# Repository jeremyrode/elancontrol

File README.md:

# elancontrol
### Code to control an Elan System6 Integrated Multi-Zone Controller from RaspberryPi

## FYI, I'm currently [porting the ZPad command generation to a Raspberry Pi Pico](https://github.com/jeremyrode/pico_elancontrol)

## What's in this repository:
- commandlinetools: low level software to test the bit-banging Software
- docs: notes / pictures / MATLAB data
- InterfacePCB: Eagle Files to build RaspberryPi HAT interface to the 6 x RJ-45 connectors
- nodejsserver: Code for the control system

### Hardware:

- [x] Reverse Engineer IR Control Protocol
- [x] Create Function to Replicate IR Control on RaspPi GPIO
- [x] Design Electrical Level Shifter for IR Protocol
- [x] Write UDP server that listens for commands and sends via GPIO
- [x] Verify GPIOs can be used on Pi2
- [x] Verify RS-485 identical on all 6 zones.
- [x] Design RaspPi "Hat" PCB with 6 x Level Shifters and 1 x RS-485
- [x] Test RaspPi "Hat"

### Software:

- [x] Interface Node.js to bit banging C software via N-API
- [x] Node.js server via Websockets
- [x] Webpage GUI with Websockets interface to the Node.js backend
- [x] Reverse Engineer RS-485 based Status Protocol to display current state

## Current Status
Full command sending functionality achieved:

HTML Frontend /JavaScript ->  Websocket -> Node.js Sever -> Via N-API -> C Bitbang GPIO -> Custom Level Shifter pcb

Status packet and reporting functionality achieved:

 RS-485 -> SerialPort (node.js) -> Delimiter Parser (node.js) -> Websocket -> HTML Frontend /JavaScript

## General Info
I have a Elan S6 in my house and I love it, if only I could control it via my phone!  It shouldn't be that hard to get a Pi connected!

## Inital Feasibility
This initial goal is to have a Raspberry inject IR commands from a bit banged GPIO.  I'm going to capture the commands from the Zpad, and see if a Pi can bit bang fast enough to replicate them.  Unfortunately, it looks like pin#2 uses an open collector pull up to 12V.  We will need a level shifter and a PMOS pull-up.  I will build a level shifter, and test if we can command the S6

Looking at the commands, they consist of 12 x 12.5 us wide 12V high pulses, with either 5.07 ms spacing (short) or 7.6 ms of spacing (long).
The first 6 pulses seem to be a preamble, always spaced short, then the next 6 with either long or short:

Decoding of the Key Commands (Preamble Omitted):

| Command  | Code | Bin | Dec |
| :------: |:----:|:---:|:---:|
| Power | SSSSSS | 000000 | 0 |
| Mute | SSSSLS | 000010 | 2 |
| VolUp | SSSLSS | 000100 | 4 |
| VolDown | LSSLSS | 100100 | 36 |
| 2ndRowRight | LSLSSS | 101000 | 40 |
| 2ndRowCenter | SSLLSS | 001100 | 12 |
| 2ndRowLeft | SSLSLL | 001011 | 11 |
| UpperRight | SSLSLS | 001010 | 10 |
| UpperCenter | SSLSSL | 001001 | 9 |
| UpperLeft | SSLSSS | 001000 | 8 |

## Level Shifter

Circuit takes the 3.3V GPIO from the Pi, and preforms a open-collector pull-up.  The S6 seems to have an internal 1k pull-down to ground.  Looking at the Zpads, they have an open-collector pull-up with a ~100 ohm resistor to current limit.  Added a dual diode for over-voltage protection (The Zpads have diode protection as well).

I also prototyped it with some components I had laying around:

## PCB

Trusty old Macrofab!

Known issues:  The bottom row of Cat5 Is hard to get out, as the Cat5 connectors are supposed to hang off the edge of the PCB.  This would make the PCB huge, if I'm still trying to use all 4 mounting holes.  No good way to solve this.  Need a very high [Rasperry Pi connector](https://www.amazon.com/gp/product/B0756KM3GB/ref=oh_aui_search_detailpage?ie=UTF8&psc=1) to clear (this one is barley tall enough).

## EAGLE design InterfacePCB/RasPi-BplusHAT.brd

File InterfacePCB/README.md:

# PCB
For some reason this is an incompleate version?

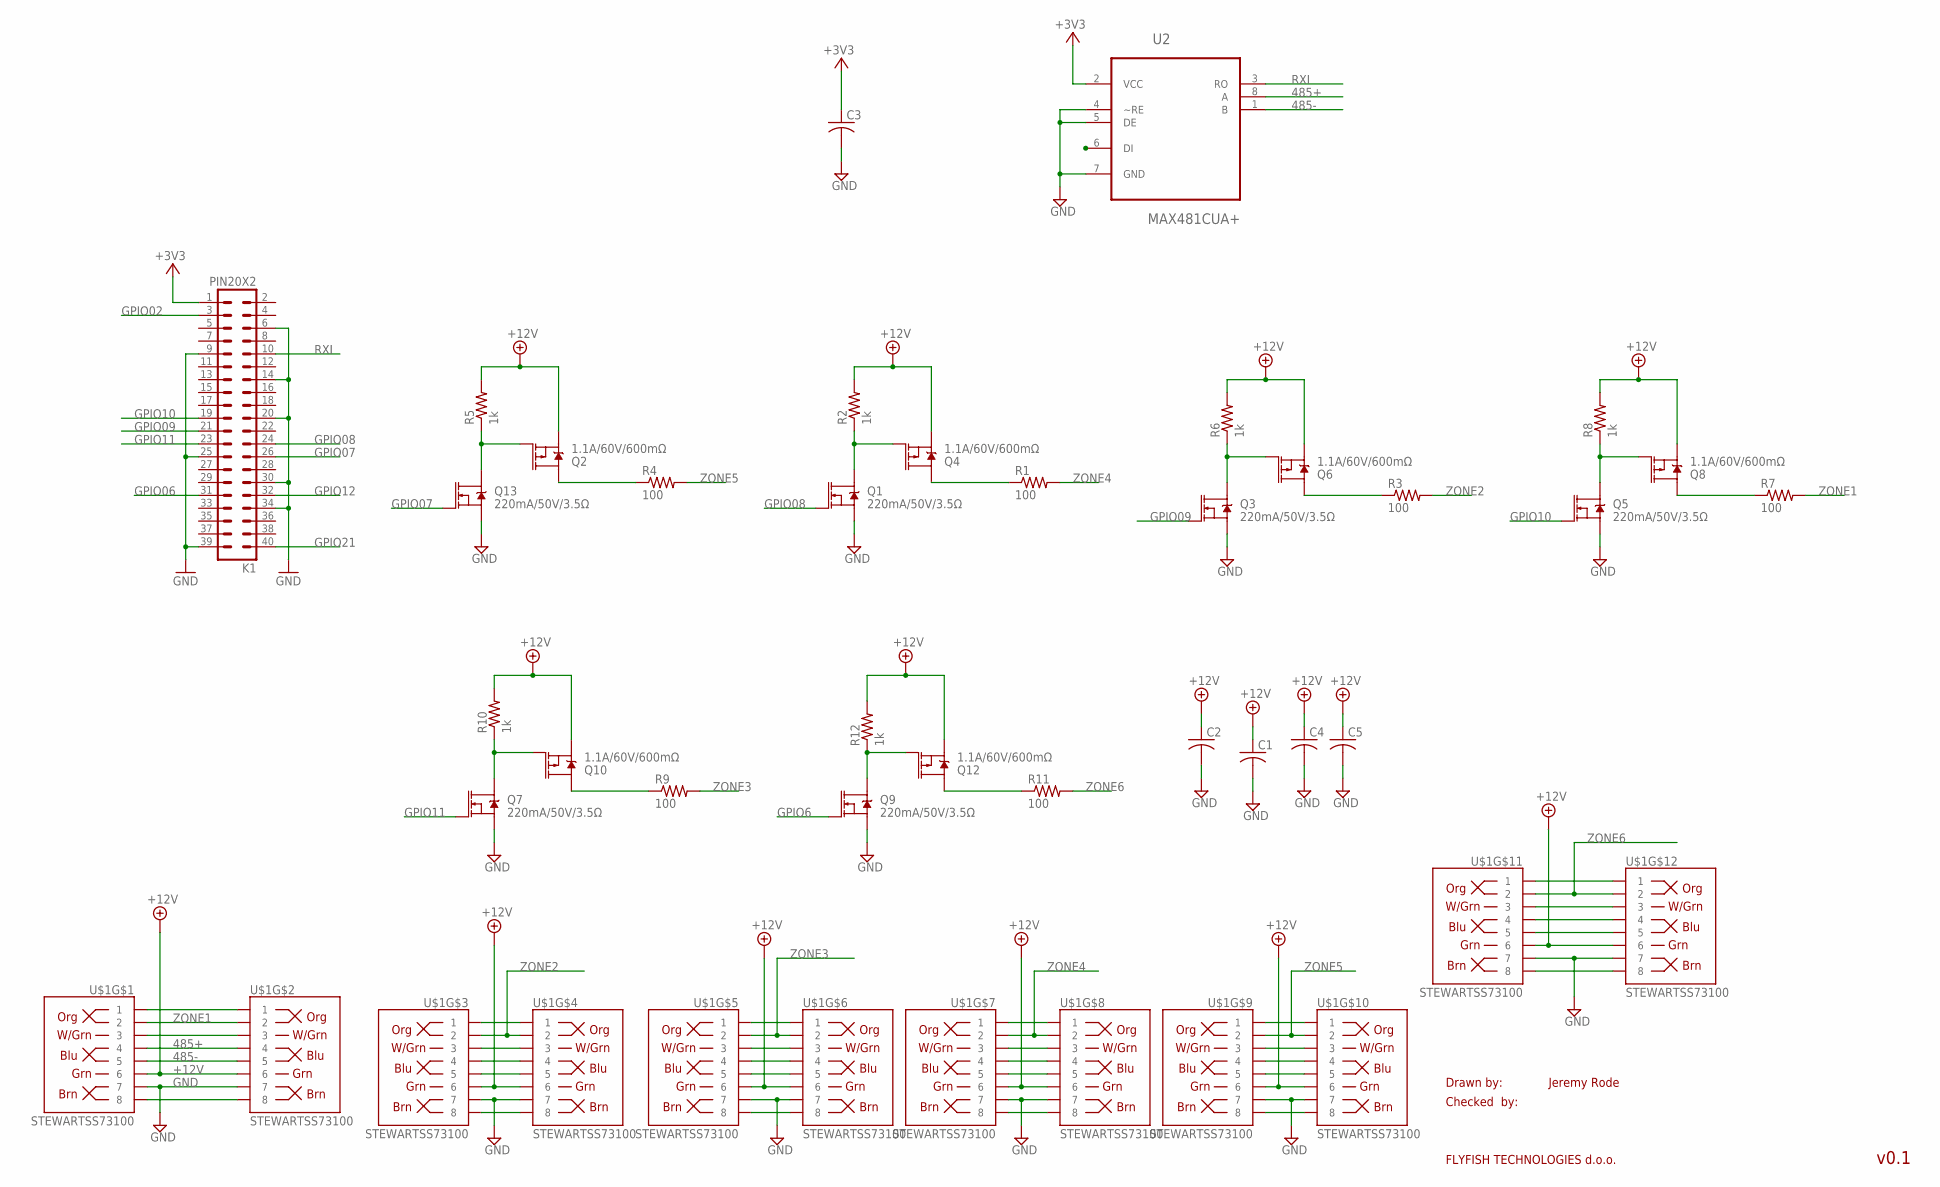
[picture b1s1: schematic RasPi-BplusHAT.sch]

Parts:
C1, C2, C3, C4, C5: C-USC0805; C0805
K1: PIN20X2; PIN_20X2
Q1, Q3, Q5, Q7, Q9, Q13: 220mA/50V/3.5Ω; SOT23-3
Q2, Q4, Q6, Q8, Q10, Q12: 1.1A/60V/600mΩ; SOT23-3
R1, R3, R4, R7, R9, R11: 100; R0805
R2, R5, R6, R8, R10, R12: 1k; R0805
U2: MAX481CUA+; SOP65P490X110-8N
U$1: STEWARTSS73100

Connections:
485+: U2.8 (A), U$1.P$4 (4), U$1.P$12 (4)
485-: U2.1 (B), U$1.P$5 (5), U$1.P$13 (5)
+3V3: C3.1, K1.1, U2.2 (VCC)
+12V: C1.1, C2.1, C4.1, C5.1, Q2.2 (S), Q4.2 (S), Q6.2 (S), Q8.2 (S), Q10.2 (S), Q12.2 (S), R2.2, R5.2, R6.2, R8.2, R10.2, R12.2, U$1.P$6 (6), U$1.P$14 (6), U$1.P$22 (6), U$1.P$30 (6), U$1.P$38 (6), U$1.P$46 (6), U$1.P$54 (6), U$1.P$62 (6), U$1.P$70 (6), U$1.P$78 (6), U$1.P$86 (6), U$1.P$94 (6)
GND: C1.2, C2.2, C3.2, C4.2, C5.2, K1.6, K1.9, K1.14, K1.20, K1.25, K1.30, K1.34, K1.39, Q1.2 (S), Q3.2 (S), Q5.2 (S), Q7.2 (S), Q9.2 (S), Q13.2 (S), U2.4 (~RE), U2.5 (DE), U2.7 (GND), U$1.P$7 (7), U$1.P$15 (7), U$1.P$23 (7), U$1.P$31 (7), U$1.P$39 (7), U$1.P$47 (7), U$1.P$55 (7), U$1.P$63 (7), U$1.P$71 (7), U$1.P$79 (7), U$1.P$87 (7), U$1.P$95 (7)
GPIO02: K1.3
GPIO6: Q9.1 (G)
GPIO06: K1.31
GPIO07: K1.26, Q13.1 (G)
GPIO08: K1.24, Q1.1 (G)
GPIO09: K1.21, Q3.1 (G)
GPIO10: K1.19, Q5.1 (G)
GPIO11: K1.23, Q7.1 (G)
GPIO12: K1.32
GPIO21: K1.40
unnamed: Q1.3 (D), Q4.1 (G), R2.1
unnamed: Q4.3 (D), R1.1
unnamed: Q3.3 (D), Q6.1 (G), R6.1
unnamed: Q2.1 (G), Q13.3 (D), R5.1
unnamed: Q2.3 (D), R4.1
unnamed: Q6.3 (D), R3.1
unnamed: Q5.3 (D), Q8.1 (G), R8.1
unnamed: Q8.3 (D), R7.1
unnamed: Q7.3 (D), Q10.1 (G), R10.1
unnamed: Q10.3 (D), R9.1
unnamed: Q9.3 (D), Q12.1 (G), R12.1
unnamed: Q12.3 (D), R11.1
unnamed: U$1.P$1 (1), U$1.P$9 (1)
unnamed: U$1.P$3 (3), U$1.P$11 (3)
unnamed: U$1.P$17 (1), U$1.P$25 (1)
unnamed: U$1.P$19 (3), U$1.P$27 (3)
unnamed: U$1.P$20 (4), U$1.P$28 (4)
unnamed: U$1.P$21 (5), U$1.P$29 (5)
unnamed: U$1.P$33 (1), U$1.P$41 (1)
unnamed: U$1.P$35 (3), U$1.P$43 (3)
unnamed: U$1.P$36 (4), U$1.P$44 (4)
unnamed: U$1.P$37 (5), U$1.P$45 (5)
unnamed: U$1.P$8 (8), U$1.P$16 (8)
unnamed: U$1.P$49 (1), U$1.P$57 (1)
unnamed: U$1.P$51 (3), U$1.P$59 (3)
unnamed: U$1.P$52 (4), U$1.P$60 (4)
unnamed: U$1.P$53 (5), U$1.P$61 (5)
unnamed: U$1.P$65 (1), U$1.P$73 (1)
unnamed: U$1.P$67 (3), U$1.P$75 (3)
unnamed: U$1.P$68 (4), U$1.P$76 (4)
unnamed: U$1.P$69 (5), U$1.P$77 (5)
unnamed: U$1.P$81 (1), U$1.P$89 (1)
unnamed: U$1.P$83 (3), U$1.P$91 (3)
unnamed: U$1.P$84 (4), U$1.P$92 (4)
unnamed: U$1.P$85 (5), U$1.P$93 (5)
unnamed: U$1.P$24 (8), U$1.P$32 (8)
unnamed: U$1.P$40 (8), U$1.P$48 (8)
unnamed: U$1.P$56 (8), U$1.P$64 (8)
unnamed: U$1.P$72 (8), U$1.P$80 (8)
unnamed: U$1.P$88 (8), U$1.P$96 (8)
RXI: K1.10, U2.3 (RO)
ZONE1: R7.2, U$1.P$2 (2), U$1.P$10 (2)
ZONE2: R3.2, U$1.P$18 (2), U$1.P$26 (2)
ZONE3: R9.2, U$1.P$34 (2), U$1.P$42 (2)
ZONE4: R1.2, U$1.P$50 (2), U$1.P$58 (2)
ZONE5: R4.2, U$1.P$66 (2), U$1.P$74 (2)
ZONE6: R11.2, U$1.P$82 (2), U$1.P$90 (2)

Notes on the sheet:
Drawn by:
Checked by:
FLYFISH TECHNOLOGIES d.o.o.
Jeremy Rode
v0.1

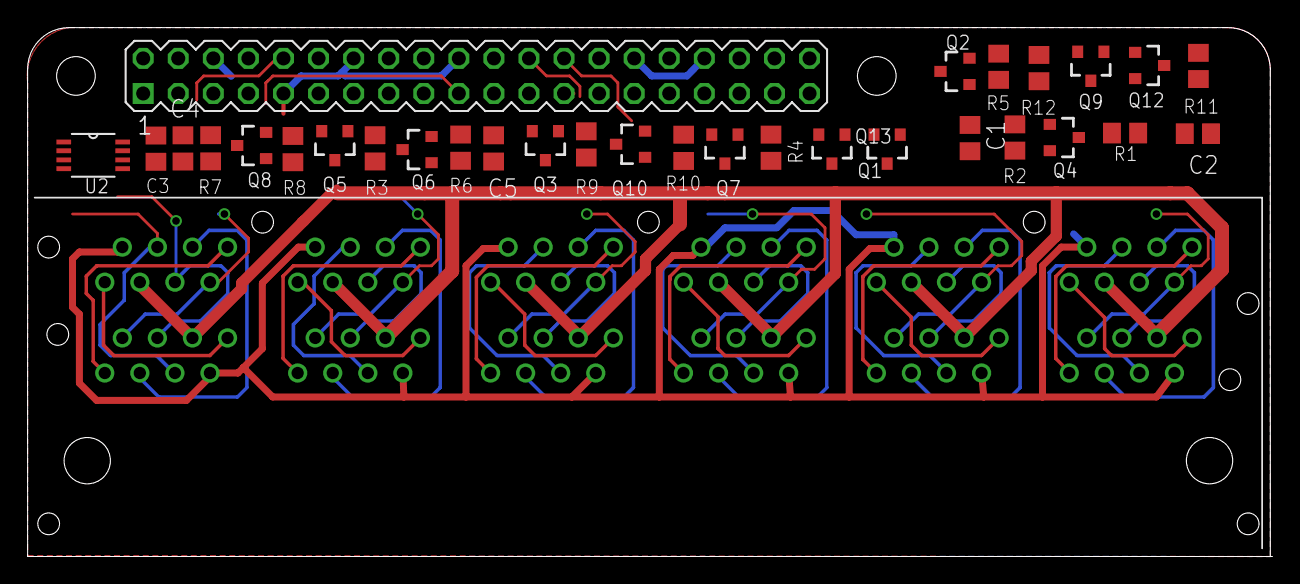
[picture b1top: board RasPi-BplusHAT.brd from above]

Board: 2 copper layers, 90.2 x 38.3 mm, 32 parts (0 on the bottom side), 57 nets.

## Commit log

2018-02-27 Inital code dump into git
2018-02-27 Readme
2018-02-27 Prelim Readme
2018-02-28 Clean up Volume Up
2018-02-28 Added start of C function to TX arb Zpad commands
2018-02-28 Added makefile and outline of c++ server
2018-03-01 Work on arb command c test and decoding
2018-03-01 Fixed tale
2018-03-01 fix table
2018-03-01 Fixed long short inversion
2018-03-01 Command line command sender
2018-03-01 send_zpad_command working and tested
2018-03-01 Update MATLAB decoder
2018-03-01 Testing C++ call
2018-03-01 compling sucessfully
2018-03-01 C++ calling C works
2018-03-01 Update makefile to build c++ test
2018-03-02 python sender
2018-03-02 UDP work
2018-03-02 udp handler
2018-03-02 UDP recieve working
2018-03-02 UDP responder working
2018-03-02 Breaking recieve into bytes
2018-03-02 End to end working
2018-03-02 Multipin support but only 7-11 working
2018-03-02 Trying to get more than 5 pins
2018-03-02 Only 7-11 GPIO pins work
2018-03-03 Start of PCB Schematic
2018-03-03 Add Schematic to readme
2018-03-04 PCB Work
2018-03-04 Board Layout
2018-03-04 12 RJ45 pcb decal
2018-03-04 Fix pin numberbing on rj45
2018-03-04 Fixed pin inversion
2018-03-10 PCB Update
2018-03-13 Finished PCB
2018-03-13 Ignore Eagle Backup files
2018-03-13 Progress, and the pin numbering statement was incorrect
2018-03-13 Final v1 Board, as ordeded Minor PCB changes
2018-03-13 Fixed pin inilization all GPIOS now work
2018-03-13 Added channel selection to server
2018-03-14 UDP server works on all GPIO channels
2018-03-14 Started Web GUI Interface
2018-03-28 Results from testing PCB
2018-03-30 Fixed inverted PMOS in schematic
2018-04-06 Reworking Board smaller
2018-04-12 ignore autoroute
2018-12-01 Update level shifter in docs
2019-01-09 nodejs start
2019-01-09 Node JS testing
2019-01-09 node js work, api seg faults
2019-01-09 changed img filename
2019-01-09 added PCB photo
2019-01-09 N-API Working
2019-01-11 Added websocket examples
2019-01-11 Initial Node JS Websockets working
2019-01-12 Websockets working
2019-01-12 file cleanup
2019-01-12 Directory Cleanup
2019-01-15 Working though Websocket to N-API
2019-01-15 Inital Operation Achieved!
2019-01-17 Only mmap once, moved to different IP ranges
2019-02-02 Filename Cleanup, break out javascript
2019-02-02 cleanup and rename
2019-02-02 readme cleanup
2019-02-03 Major C cleanup
2019-02-03 More code cleanup
2019-02-03 namechange
2019-02-12 Make serial diff
2019-02-15 serial upgrades
2019-02-17 Getting Volume from status packet
2019-02-17 Status packet fully decoded
2019-02-18 status update inital operation
2019-02-18 full functionality
2019-02-23 On/Off detection, client culling
2019-05-30 Minor changes during testing
2019-10-24 frontend updates
2019-10-26 Moved new frontend to index_new.html for testing
2019-12-21 Testing Smartthings
2020-03-31 Adding slider functionality 1
2020-04-03 sliders working but open loop
2020-04-03 Upgraded slider to recursive, handle missing codes, general code cleanup
2020-12-24 IP Changes smartthings work
2020-12-27 Initial checking for smartthings work
2020-12-27 Master cleanup
2020-12-27 Cleanup
2021-10-26 check in before code cleanup
2021-10-26 Logging changes and variable dec cleanup
2023-09-21 Remove missing volume codes from slider target values

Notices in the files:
parts and their libraries:
SparkFun-DiscreteSemi: Licensing: Creative Commons ShareAlike 4.0 International - https://creativecommons.org/licenses/by-sa/4.0
